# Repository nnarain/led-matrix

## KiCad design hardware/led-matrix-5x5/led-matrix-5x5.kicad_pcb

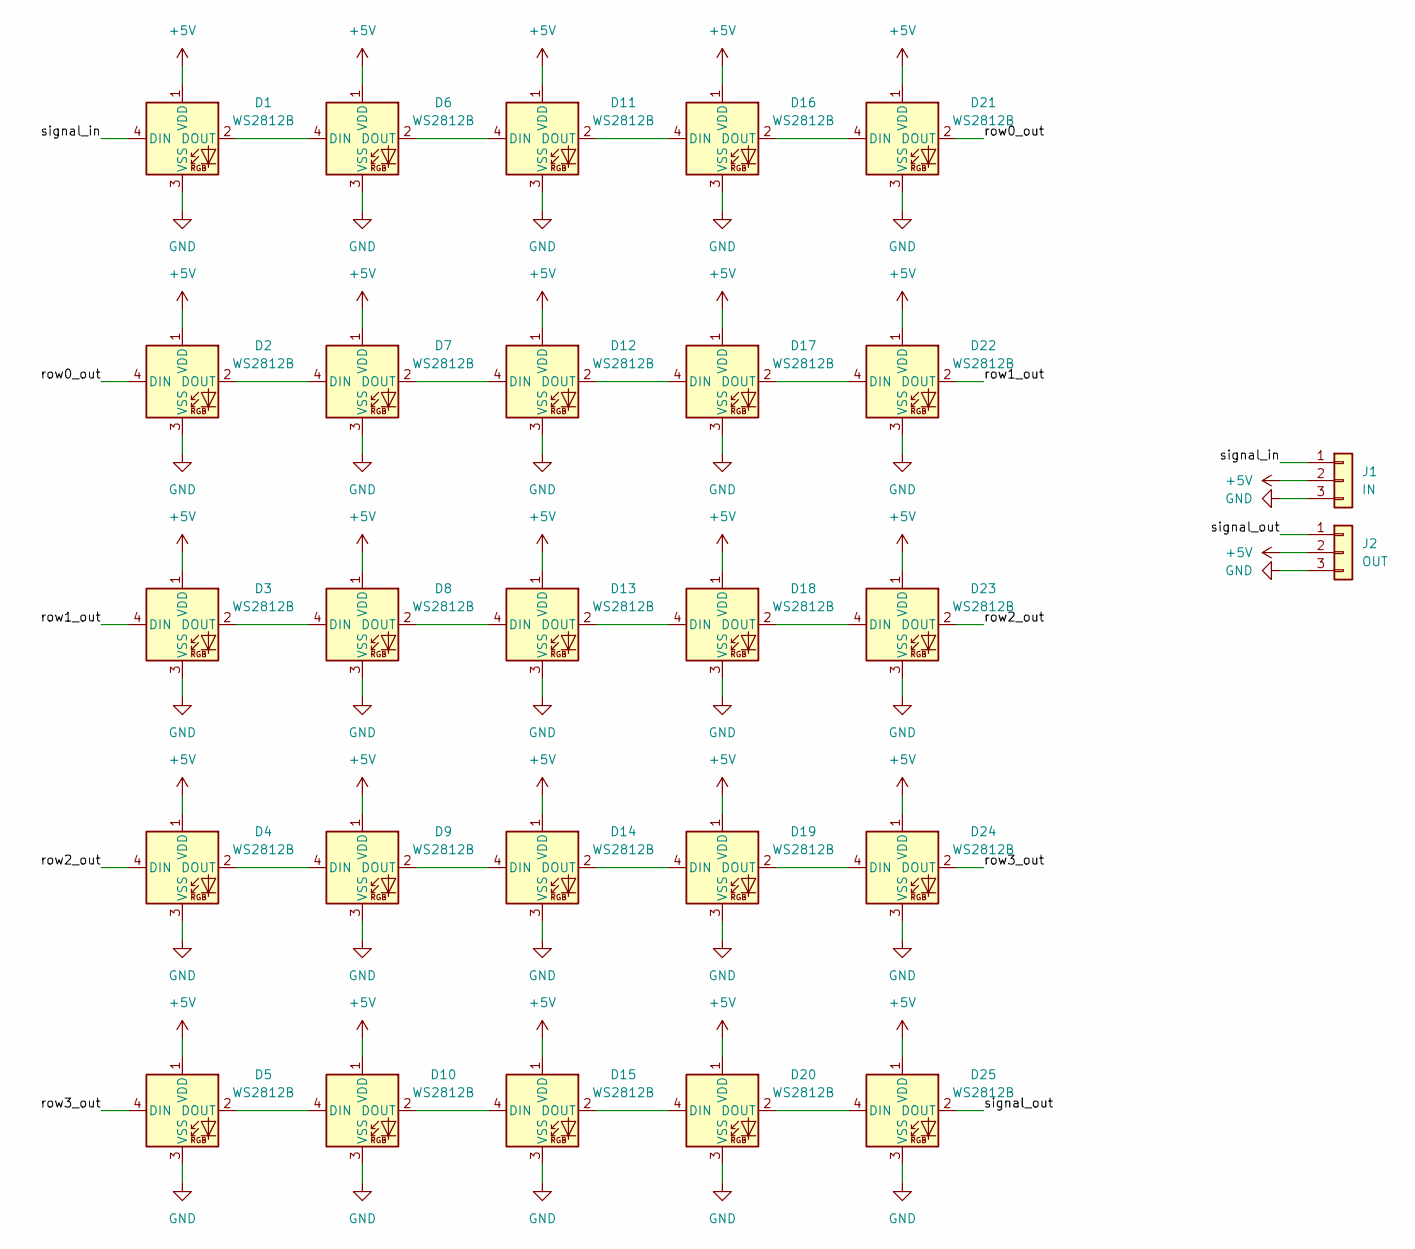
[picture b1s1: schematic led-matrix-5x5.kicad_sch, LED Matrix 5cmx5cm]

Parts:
D1, D2, D3, D4, D5, D6, D7, D8, D9, D10, D11, D12, D13, D14, D15, D16, D17, D18, D19, D20, D21, D22, D23, D24, D25: WS2812B; LED_WS2812B_PLCC4_5.0x5.0mm_P3.2mm; LCSC C2761795
J1: IN; MatrixConn
J2: OUT; MatrixConn

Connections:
+5V: D1.1 (VDD), D2.1 (VDD), D3.1 (VDD), D4.1 (VDD), D5.1 (VDD), D6.1 (VDD), D7.1 (VDD), D8.1 (VDD), D9.1 (VDD), D10.1 (VDD), D11.1 (VDD), D12.1 (VDD), D13.1 (VDD), D14.1 (VDD), D15.1 (VDD), D16.1 (VDD), D17.1 (VDD), D18.1 (VDD), D19.1 (VDD), D20.1 (VDD), D21.1 (VDD), D22.1 (VDD), D23.1 (VDD), D24.1 (VDD), D25.1 (VDD), J1.2, J2.2
/row0_out: D2.4 (DIN), D21.2 (DOUT)
/row1_out: D3.4 (DIN), D22.2 (DOUT)
/row2_out: D4.4 (DIN), D23.2 (DOUT)
/row3_out: D5.4 (DIN), D24.2 (DOUT)
/signal_in: D1.4 (DIN), J1.1
/signal_out: D25.2 (DOUT), J2.1
GND: D1.3 (VSS), D2.3 (VSS), D3.3 (VSS), D4.3 (VSS), D5.3 (VSS), D6.3 (VSS), D7.3 (VSS), D8.3 (VSS), D9.3 (VSS), D10.3 (VSS), D11.3 (VSS), D12.3 (VSS), D13.3 (VSS), D14.3 (VSS), D15.3 (VSS), D16.3 (VSS), D17.3 (VSS), D18.3 (VSS), D19.3 (VSS), D20.3 (VSS), D21.3 (VSS), D22.3 (VSS), D23.3 (VSS), D24.3 (VSS), D25.3 (VSS), J1.3, J2.3
unnamed: D1.2 (DOUT), D6.4 (DIN)
unnamed: D2.2 (DOUT), D7.4 (DIN)
unnamed: D3.2 (DOUT), D8.4 (DIN)
unnamed: D4.2 (DOUT), D9.4 (DIN)
unnamed: D10.2 (DOUT), D15.4 (DIN)
unnamed: D5.2 (DOUT), D10.4 (DIN)
unnamed: D11.2 (DOUT), D16.4 (DIN)
unnamed: D6.2 (DOUT), D11.4 (DIN)
unnamed: D12.2 (DOUT), D17.4 (DIN)
unnamed: D7.2 (DOUT), D12.4 (DIN)
unnamed: D13.2 (DOUT), D18.4 (DIN)
unnamed: D8.2 (DOUT), D13.4 (DIN)
unnamed: D14.2 (DOUT), D19.4 (DIN)
unnamed: D9.2 (DOUT), D14.4 (DIN)
unnamed: D15.2 (DOUT), D20.4 (DIN)
unnamed: D16.2 (DOUT), D21.4 (DIN)
unnamed: D17.2 (DOUT), D22.4 (DIN)
unnamed: D18.2 (DOUT), D23.4 (DIN)
unnamed: D19.2 (DOUT), D24.4 (DIN)
unnamed: D20.2 (DOUT), D25.4 (DIN)

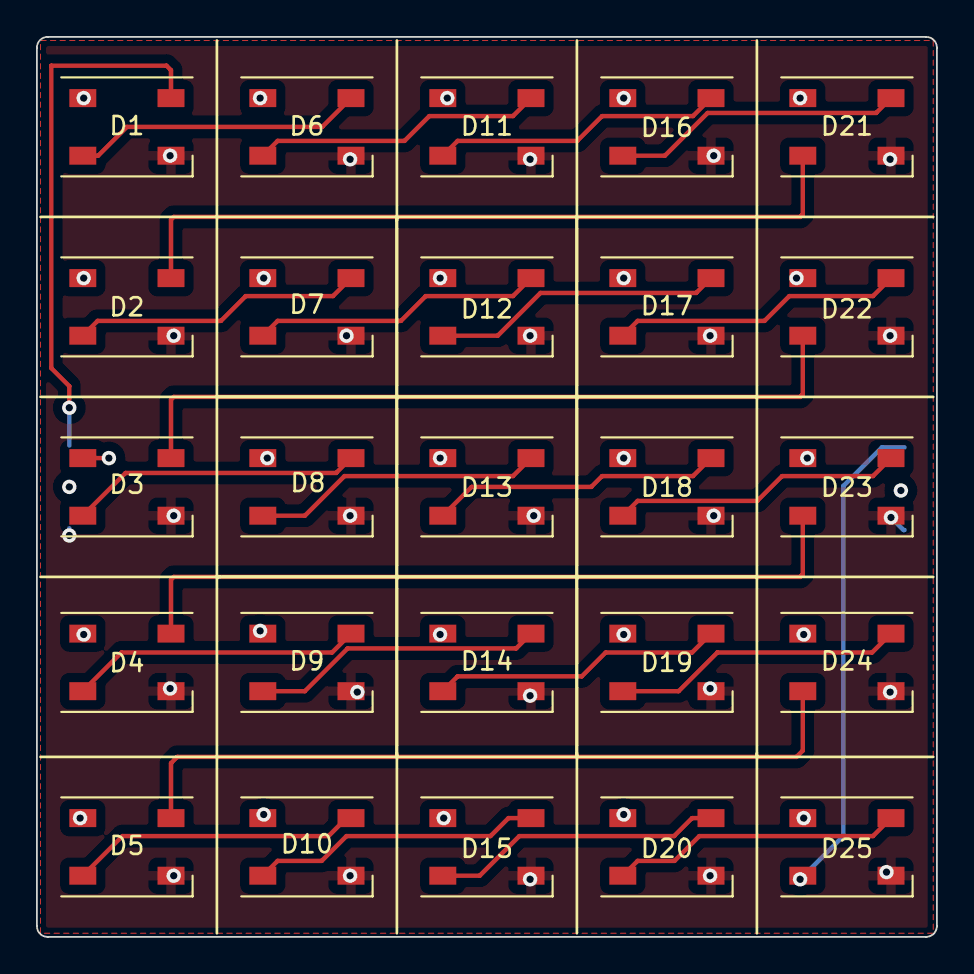
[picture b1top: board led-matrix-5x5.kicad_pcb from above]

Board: 4 copper layers, 50.0 x 50.0 mm, 27 parts (0 on the bottom side), 28 nets.
